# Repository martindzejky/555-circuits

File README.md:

# 555-circuits

A PCB design with the three most common 555 timer circuits - astable, monostable, bistable. Included in the repo are KiCad project files, the circuit and PCB design.

Here's the 3D model of the circuit design:

After an evening of soldering, here's the finished circuit board:

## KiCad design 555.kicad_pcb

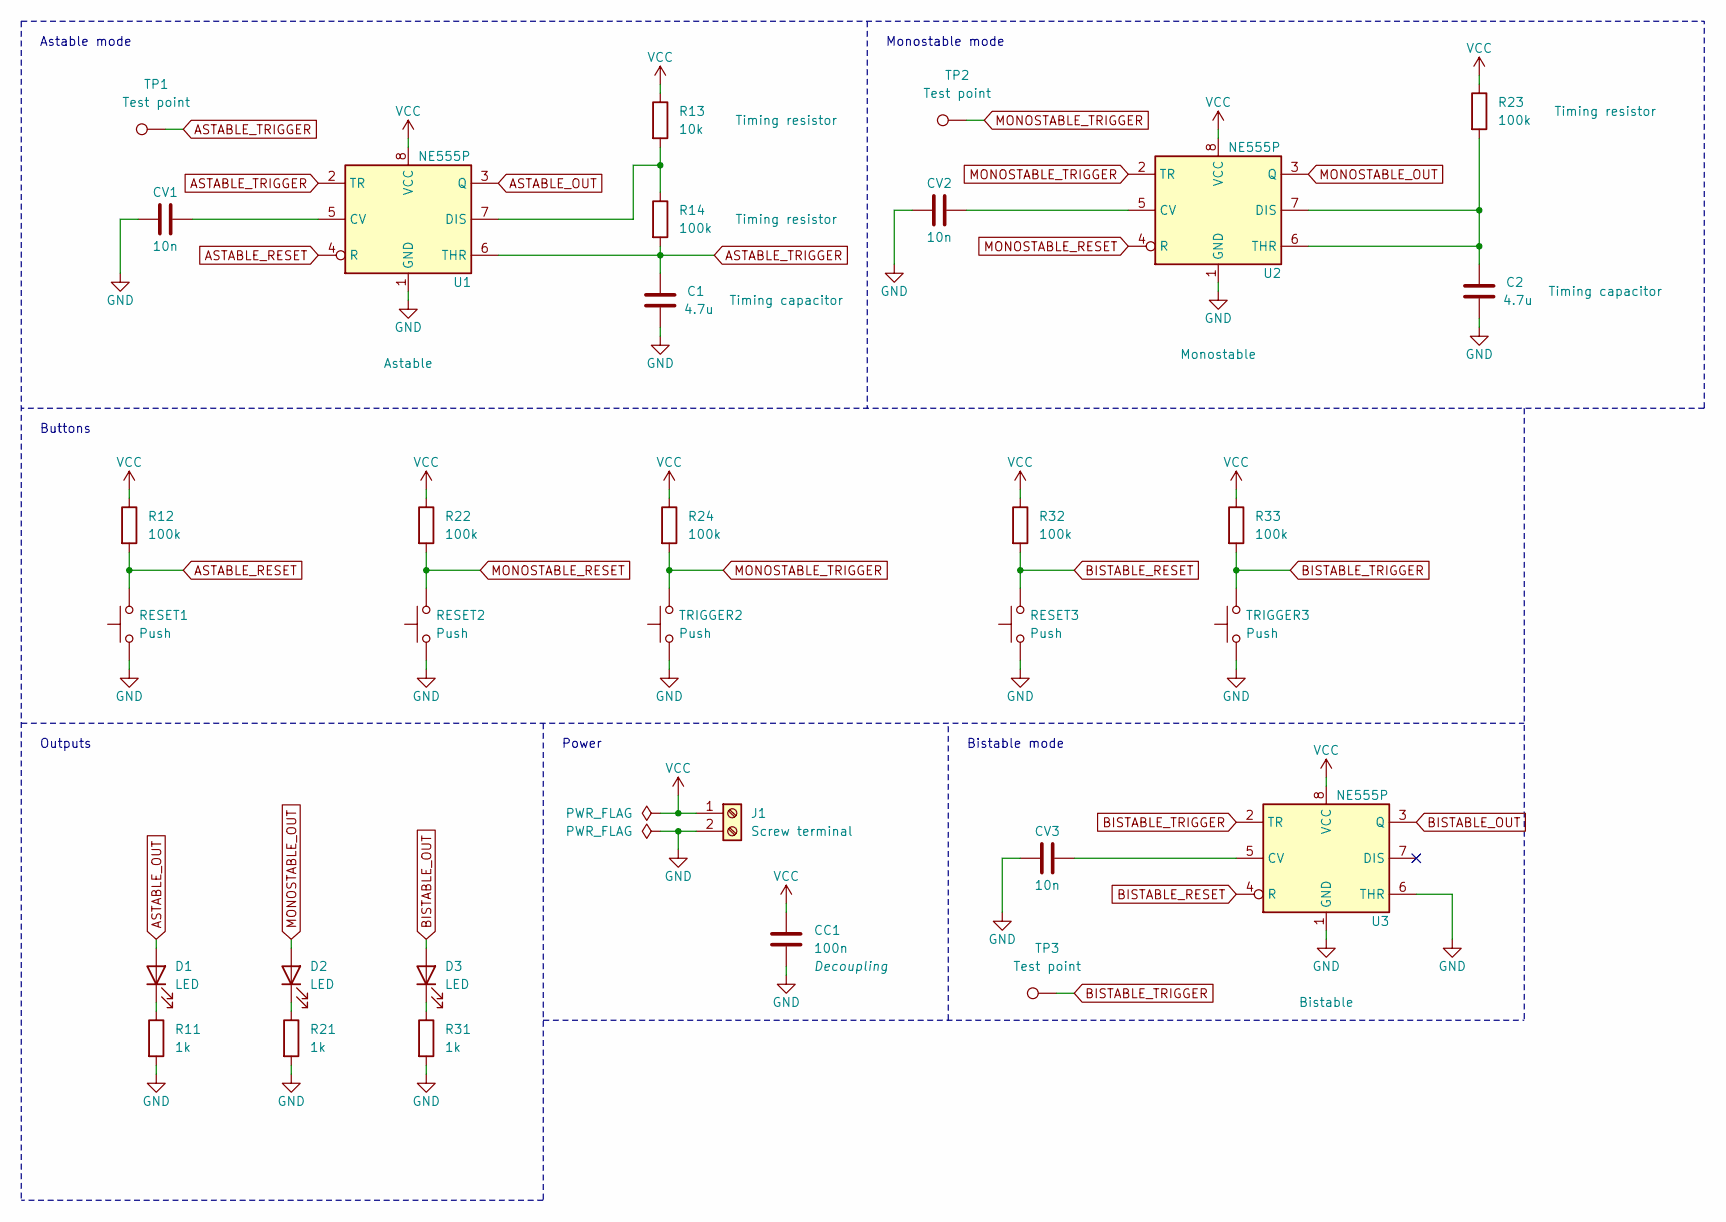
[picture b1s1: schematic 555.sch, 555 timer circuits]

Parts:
C1, C2: 4.7u; C_1206_3216Metric_Pad1.33x1.80mm_HandSolder
CC1: 100n; C_1206_3216Metric_Pad1.33x1.80mm_HandSolder
CV1, CV2, CV3: 10n; C_1206_3216Metric_Pad1.33x1.80mm_HandSolder
D1, D2, D3: LED; LED_1210_3225Metric_Pad1.42x2.65mm_HandSolder
J1: Screw terminal; TerminalBlock_RND_205-00045_1x02_P5.00mm_Horizontal
R11, R21, R31: 1k; R_1206_3216Metric_Pad1.30x1.75mm_HandSolder
R12, R14, R22, R23, R24, R32, R33: 100k; R_1206_3216Metric_Pad1.30x1.75mm_HandSolder
R13: 10k; R_1206_3216Metric_Pad1.30x1.75mm_HandSolder
RESET1, RESET2, RESET3: Push; SW_PUSH_6mm
TP1, TP2, TP3: Test point; TestPoint_Pad_D2.0mm
TRIGGER2, TRIGGER3: Push; SW_PUSH_6mm
U1, U2, U3: NE555P; DIP-8_W7.62mm

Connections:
ASTABLE_OUT: D1.2 (A), U1.3 (Q)
ASTABLE_RESET: R12.2, RESET1.2, U1.4 (R)
ASTABLE_TRIGGER: C1.2, R14.2, TP1.1, U1.2 (TR), U1.6 (THR)
BISTABLE_OUT: D3.2 (A), U3.3 (Q)
BISTABLE_RESET: R32.2, RESET3.2, U3.4 (R)
BISTABLE_TRIGGER: R33.2, TP3.1, TRIGGER3.2, U3.2 (TR)
GND: C1.1, C2.1, CC1.1, CV1.2, CV2.2, CV3.2, J1.2, R11.2, R21.2, R31.2, RESET1.1, RESET2.1, RESET3.1, TRIGGER2.1, TRIGGER3.1, U1.1 (GND), U2.1 (GND), U3.1 (GND), U3.6 (THR)
MONOSTABLE_OUT: D2.2 (A), U2.3 (Q)
MONOSTABLE_RESET: R22.2, RESET2.2, U2.4 (R)
MONOSTABLE_TRIGGER: R24.2, TP2.1, TRIGGER2.2, U2.2 (TR)
unnamed: C2.2, R23.2, U2.6 (THR), U2.7 (DIS)
unnamed: CV1.1, U1.5 (CV)
unnamed: CV2.1, U2.5 (CV)
unnamed: CV3.1, U3.5 (CV)
unnamed: D1.1 (K), R11.1
unnamed: D2.1 (K), R21.1
unnamed: D3.1 (K), R31.1
unnamed: R13.2, R14.1, U1.7 (DIS)
VCC: CC1.2, J1.1, R12.1, R13.1, R22.1, R23.1, R24.1, R32.1, R33.1, U1.8 (VCC), U2.8 (VCC), U3.8 (VCC)

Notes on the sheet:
Outputs
Buttons
Bistable mode
Monostable mode
Astable mode
Power

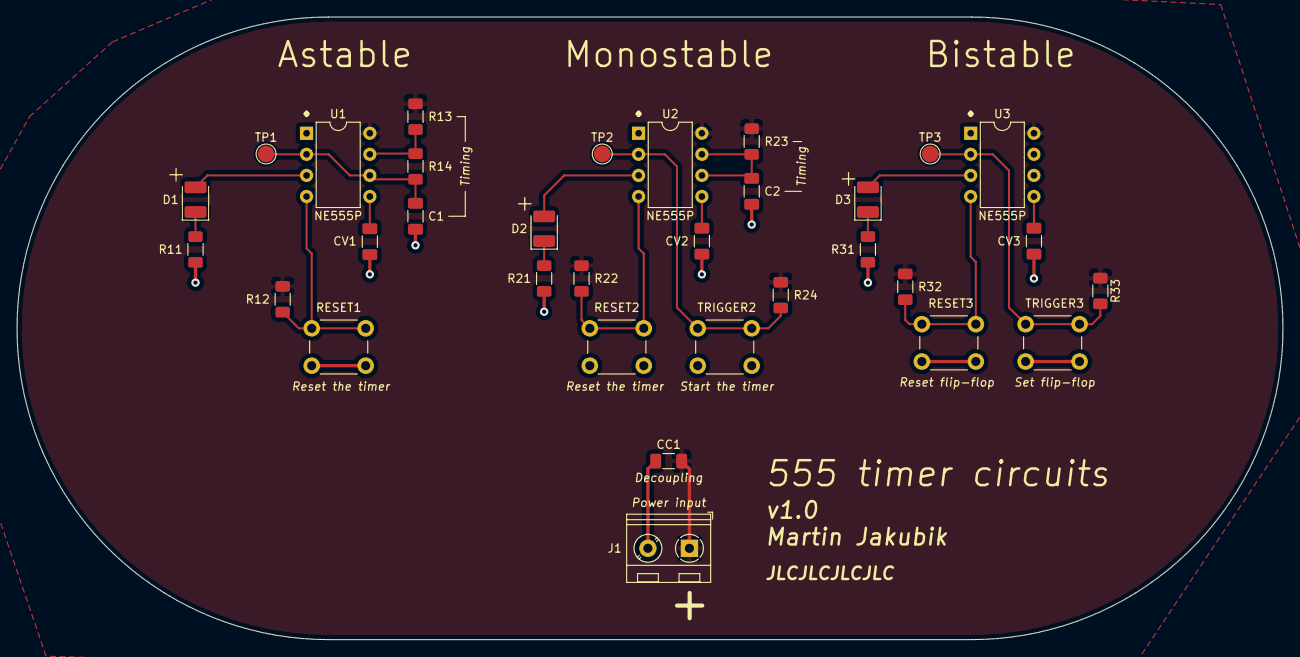
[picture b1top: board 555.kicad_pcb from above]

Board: 2 copper layers, 152.5 x 75.0 mm, 32 parts (0 on the bottom side), 19 nets.

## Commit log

2021-01-03 add project files
2021-01-03 add 3d model image
2021-07-23 add photos of the finished project
2021-07-23 add photos to README
